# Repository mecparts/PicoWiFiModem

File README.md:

# Pico WiFi modem

## A Pico W based RS232 \<-\> WiFi modem with Hayes AT style commands and LED indicators

|  |
|:--:|
| The Pico WiFi modem |

This project began as an exercise to learn about the Pico W and lwIP.
Then, as I figured things out, it sort of took on a life of its own...

The code was ported from my 
[Retro WiFi Modem](https://github.com/mecparts/RetroWiFiModem). 
One look at it will betray its Arduino IDE origin! It's definitely not
the most efficient way to do things in the Pico world, but it worked
well enough for my purposes in learning "okay, I know what I want to do
here, but how does the Pico C/C++ SDK do it?"

It likely would have been much faster to install one of the Pico-Arduino
cores. I imagine there would have been far fewer code changes. But I
don't think I would have learned anywhere near as much about the
workings of the Pico W and lwIP as I did by using the Pico SDK.

## The Hardware

|  |
|:--:|
| The prototype |

As with the code, I re-up'd a lot of the original hardware decisions.
But, since this time around it wasn't a pandemic project that I was 
trying to do as much as possible with parts on hand, I used a MAX3237
instead of a MAX3232.

|  |
|:--:|
| The interior |

The modem still uses the classic Hayes style blinking LEDs and a DE-9F
for the RS-232 connector. Everything is displayed: RTS, CTS, DSR, DTR,
DCD, RI, TxD and RxD. And this time, since I used a MAX3237, they're all
brought out to the DE-9F connector. So things like using a change in the
DTR line to go to command mode or end a call are supported (on a system
that brings DTR out to the serial port, of course).

Since the Pico W doesn't have EEPROM on board, I added a small 4K I2C
EEPROM to the mix. I could have used a block of the Pico's flash, but I
wanted to get a feel for I2C on the Pico as well.

The Pico is socketed on this first board due to the lack of OTA
programming. The PCB is set up to allow it to be soldered directly on
the board once I have that figured out.

|  |
|:--:|
| The back panel |

The power connector expects a 2.1mm I.D. x 5.5mm O.D. barrel plug,
delivering 5 volts, centre positive.  I used a Tri-Mag L6R06H-050 (5V,
1.2A), [DigiKey part# 364-1251-ND](https://www.digikey.com/product-detail/en/tri-mag-llc/L6R06H-050/364-1251-ND/7682614).
If you plug in a 9V adapter like you'd use for an Arduino, you *will*
let the magic smoke out and have an ex-modem on your hands.

|  |
|:--:|
| The schematic |

On the off chance that there's someone else out there with a well
stocked parts box and a burning desire to put together their own Pico
WiFi modem, there's a [BOM](kicad/Pico_WiFi_Modem-bom.csv) in the
kicad sub directory. As was true with the original ESP8266 design, if
you actually had to go out and buy all the parts, it really wouldn't be
cost effective.

## The case

I re-used the same case, a Hammond 1593N case (DigiKey part #
[HM963-ND](https://www.digikey.com/en/products/detail/hammond-manufacturing/1593NBK/1090774)
or [HM964-ND](https://www.digikey.com/en/products/detail/hammond-manufacturing/1593NGY/1090775)
depending on whether you like black or grey). STL and OpenSCAD
files are included for the front and back panels. You could use the
proper Hammond red panel for the front (DigiKey part #
[HM965-ND](https://www.digikey.com/en/products/detail/hammond-manufacturing/1593NIR10/1090776)),
*but* they're only available in 10 packs and their price is highway robbery.
I ended up using a slightly smaller red panel (DigiKey part #
[HM889-ND](https://www.digikey.com/en/products/detail/hammond-manufacturing/1593SIR10/409899))
that was ~much~ cheaper (it has recently increased in price by 500%)
and available in single units.

The labels are unbelievably low tech. I print them on a piece of inkjet
transparency film. I then cut that down to size so that it will fit
under the LED opening. Then I attach the trimmed down transparency piece
to a length of matte finish, invisible tape and carefully position it in
place. A bit of careful work with an x-acto knife and you've got
yourself a label that looks like it's part of the panel. If you look
closely at the front panel image you can see the edges of the
transparency film and the tape, but in practice they both essentially
disappear.

## The PCB

The PCB includes cutouts for the two columns that join the case
together, and mounting holes for the 6 standoffs. Also, there's an oddly
shaped cutout in back end to allow a particular IDC DE-9F I had on hand.
It's available from DigiKey (or a very close clone is) but it's fairly
pricey. But there's plenty of room for an ordinary solder cup DE-9F.
You'd most likely want to omit the 10 pin header and just wire the DE-9F
right to the board.

Unlike the original Retro Wifi Modem, I made no attempt to make this
board by hand. Instead, I took advantage of an introductory offer by a
well known PCB house and had PCBs made. 5 boards for under 20 bucks, and
delivered in under a week? Who could say no?

## The Software

|  |
|:--:|
| Modem command list |

The software is naturally quite similar to the original ESP8266 Wifi
modem. There are a few changes (and one fairly major omission):

* DTR signal handling (AT&D)
* Escape sequence character definition (ATS2)
* no OTA reprogramming (yet!)

### First time setup

The default serial configuration is 9600bps, 8 data bits, no parity, 1
stop bit.

Here's the commands you need to set up the modem to automatically
connect to your WiFi network:

1. `AT$SSID=your WiFi network name` to set the WiFi network that the
modem will connect to when it powers up.
2. `AT$PASS=your WiFi network password` to set the password for the
network.
3. `ATC1` to connect to the network.
4. Optional stuff:
   * `AT$SB=speed` to set the default serial speed.
   * `AT$SU=dps` to set the data bits, parity and stop bits.
   * `ATNETn` to select whether or not to use Telnet protocol.
   * `AT&Kn` to use RTS/CTS flow control or not.
   * `AT&Dn` to set up DTR handling.
5. `AT&W` to save the settings.

Once you've done that, the modem will automatically connect to your WiFi
network on power up and will be ready to "dial up" a connection with
ATDT.

### Command Reference

Multiple AT commands can be typed in on a single line. Spaces between
commands are allowed, but not within commands (i.e. AT S0=1 X1 Q0 is
fine; ATS 0=  1 is not). Commands that take a string as an argument
(e.g. AT$SSID=, AT$TTY=) assume that *everything* that follows is a part
of the string, so no commands are allowed after them.

Command | Details
------- | -------
+++     | Online escape code. Once your modem is connected to another device, the only command it recognises is an escape code of a one second pause followed by three typed plus signs and another one second pause, which puts the modem back into local command mode.
A/      | Repeats the last command entered. Do not type AT or press Enter.
AT      | The attention prefix that precedes all command except A/ and +++.
AT?     | Displays a help cheatsheet.
ATA     | Force the modem to answer an incoming connection when the conditions for auto answer have not been satisfied.
ATC?<br>ATC*n* | Query or change the current WiFi connection status. A result of 0 means that the modem is not connected to WiFi, 1 means the modem is connected. The command ATC0 disconnects the modem from a WiFi connection. ATC1 connects the modem to the WiFi.
ATDS*n* | Calls the host specified in speed dial slot *n* (0-9).
ATDT<i>[+=-]host[:port]</i> | Tries to establish a WiFi TCP connection to the specified host name or IP address. If no port number is given, 23 (Telnet) is assumed. You can also use ATDT to dial one of the speed dial slots in one of two ways:<br><br><ul><li>The alias in each speed dial slot is checked to see if it matches the specified hostname.</li><li>A host specified as 7 identical digits dials the slot indicated by the digit. (i.e. 2222222 would speed dial the host in slot 2).</li></ul>Preceding the host name or IP address with a +, = or - character overrides the ATNET setting for the period of the connection.<br><br><ul><li>**+** forces NET2 (fake Telnet)</li><li>**=** forces NET1 (real Telnet)</li><li>**-** forces NET0 (no Telnet)</li></ul>Once the dial attempt has begun, pressing any key before the connection is established will abort the attempt.
ATE?<br>ATE*n* | Command mode echo. Enables or disables the display of your typed commands.<br><br><ul><li>E0 Command mode echo OFF. Your typing will not appear on the screen.</li><li>E1 Command mode echo ON. Your typing will appear on the screen.</li></ul>
ATGET*http&#58;//host[/page]* | Displays the contents of a website page. **https** connections are not supported. Once the contents have been displayed, the connection will automatically terminate.
ATH | Hangs up (ends) the current connection.
ATI | Displays the current network status, including sketch build date, WiFi and call connection state, SSID name, IP address, and bytes transferred.
ATNET?<br>ATNET*n* | Query or change whether telnet protocol is enabled. A result of 0 means that telnet protocol is disabled; 1 is *Real* telnet protocol and 2 is *Fake* telnet protocol. If you are connecting to a telnet server, it may expect the modem to respond to various telnet commands, such as terminal name (set with `AT$TTY`), terminal window size (set with `AT$TTS`) or terminal speed. Telnet protocol should be enabled for these sites, or you will at best see occasional garbage characters on your screen, or at worst the connection may fail.<br><br>The difference between *real* and *fake* telnet protocol is this: with *real* telnet protocol, a carriage return (CR) character being sent from the modem to the telnet server always has a NUL character added after it. The implementation of the telnet protocol used by some BBSes doesn't properly strip out the NUL character. When connecting to such BBSes (Particles! is one), use *fake* telnet.<br><br>When using *real* telnet protocol, when the telnet server sends a CR character followed by a NUL character, only the CR character will be sent to the serial port; the NUL character will be silently stripped out. With *fake* telnet protocol, the NUL will be passed through.
ATO | Return online. Use with the escape code (+++) to toggle between command and online modes.
ATQ?<br>ATQ*n* | Enable or disable the display of result codes. The default is Q0.<br><br><ul><li>Q0 Display result codes.</li><li>Q1 Suppress result codes (quiet).</li></ul>
ATRD<br>ATRT | Displays the current UTC date and time from NIST in the format *YY-MM-DD HH:MM:SS*. A WiFi connection is required and you cannot be connected to another site.
ATS0?<br>ATS0=*n* | Display or set the number of "rings" before answering an incoming connection. Setting `S0=0` means "don't answer".
ATS2?<br>ATS2=*n* | Display or set the ASCII code used in the online escape sequence. The default value is 43 (the + plus character). Setting it to any value between 128 and 255 will disable the online escape function.
ATV?<br>ATV*n* | Display result codes in words or numbers. The default is V1.<br><br><ul><li>V0 Display result codes in numeric form.</li><li>V1 Display result codes in text form.</li></ul>
ATX?<br>ATX*n* | Control the amount of information displayed in the result codes. The default is X1 (extended codes).<br><br><ul><li>X0 Display basic codes (CONNECT, NO CARRIER)</li><li>X1 Display extended codes (CONNECT speed, NO CARRIER (connect time))</li></ul>
ATZ | Resets the modem.
AT&D?<br>AT&D*n* | Display or set the handling of DTR going inactive. The default is &D0 (ignored).<br><br><ul><li>&D0 Ignore</li><li>&D1 Go to command mode</li><li>&D2 End call</li><li>&D3 Reset modem</li></ul>
AT&F | Reset the NVRAM contents and current settings to the sketch defaults. All settings, including SSID name, password and speed dial slots are affected.
AT&K?<br>AT&K*n* | Data flow control. Prevents the modem's buffers for received and transmitted from overflowing.<br><br><ul><li>&K0 Disable data flow control.</li><li>&K1 Use hardware flow control. Requires that your computer and software support Clear to Send (CTS) and Request to Send (RTS) at the RS-232 interface.</li></ul>
AT&R?<br>AT&R=*server pwd* | Query or change the password for incoming connections. If set, the user has 3 chances in 60 seconds to enter the correct password or the modem will end the connection.
AT&V*n* | Display current or stored settings.<br><br><ul><li>&V0 Display current settings.</li><li>&V1 Display stored settings.</li></ul>
AT&W | Save current settings to NVRAM.
AT&Zn?<br>AT&Z*n*=*host[:port],alias* | Store up to 10 numbers in NVRAM, where *n* is the position 0-9 in NVRAM, and *host[:port]* is the host string, and *alias* is the speed dial alias name. The host string may be up to 50 characters long, and the alias string may be up to 16 characters long.<br><br>Example: `AT&Z2=particlesbbs.dyndns.org:6400,particles`<br><br>This number can then be dialed in any of the following ways:<br><br><ul><li>`ATDS2`</li><li>`ATDTparticles`</li><li>`ATDT2222222`</li></ul>
AT$AE?<br>AT$AE=*startup AT cmd* | Query or change the command line to be executed when the modem starts up.
AT$AYT | Sends a Telnet "Are You There?" command if connected to a Telnet remote.
AT$BM?<br>AT$BM=*server busy msg* | Query or change a message to be returned to an incoming connection if the modem is busy (i.e. already has a connection established).
AT$MDNS<br>AT$MDNS=*mDNS name* | Query or change the mDNS network name (defaults to "espmodem"). When a non zero TCP port is defined, you can telnet to that port with **telnet mdnsname.local port**.
AT$PASS?<br>AT$PASS=*WiFi pwd* | Query or change the current WiFi password. The password is case sensitive. Clear the password by issuing the set command with no password. The maximum length of the password is 64 characters.
AT$SB?<br>AT$SB=*n* | Query or change the current baud rate. Valid values for "n" are 110, 300, 450, 600, 710, 1200, 2400, 4800, 9600, 19200, 38400, 57600, 76800 and 115200. Any other value will return an ERROR message. The default baud rate is 1200. The Pico WiFi modem does not automatically detect baud rate like a dial-up modem. The baud rate setting must match that of your terminal to operate properly. It will display garbage in your terminal otherwise.
AT$SP?<br>AT$SP=*n* | TCP server port to listen on. A value of 0 means that the TCP server is disabled, and no incoming connections are allowed.
AT$SSID?<br>AT$SSID=*ssid name* | Query or change the current SSID to the specified name. The given SSID name is case sensitive. Clear the SSID by issuing the set command with no SSID. The maximum length of the SSID name is 32 characters.
AT$SU?<br>AT$SU=*dps* | Query or change the current number of data bits ('d'), parity ('p') and stop bits ('s") of the serial UART. Valid values for 'd' are 5, 6, 7 or 8 bits. Valid values for 'p' are (N)one, (O)dd or (E)ven parity. Valid values for 's' are 1 or 2 bits. The default settings are 8N1. The UART setting must match your terminal to work properly.
AT$TTL?<br>AT$TTL=*telnet location* | Query or change the Telnet location value to be returned when the Telnet server issues a SEND-LOCATION request. The default value is "Computer Room".
AT$TTS?<br>AT$TTS=*WxH* | Query or change the window size (columns x rows) to be returned when the Telnet server issues a NAWS (Negotiate About Window Size) request. The default value is 80x24. For terminals that are smaller than 80x24, setting these values appropriately will enable paging on the help (AT?) and network status (ATI) commands.
AT$TTY?<br>AT$TTY=*terminal type* | Query or change the terminal type to be returned when the Telnet server issues a TERMINAL-TYPE request. The default value is "ansi".
AT$W?<br>AT$W=*n* | Startup wait.<br><br><ul><li>$W=0 Startup with no wait.</li><li>$W=1 Wait for the return key to be pressed at startup.</li></ul>

### Updating the Code

As I'm writing this, I haven't settled on an OTA programming method that
I like. But I will figure something out; taking the modem apart to do a
code update will get old the very first time I have to do it. Plus,
it means that the Pico W can't be soldered down to the PCB, and that'd
be a nice to have as well.

## Status

It's a work in progress at the moment. The lack of OTA programming is
the big "needs to be done" item.

As this is my first Pico project, and the first time I've written lwIP 
stuff (and the first time I've really had to make changes to CMake 
stuff), I've run headlong into all the usual beginner gotchas. And I'm
completely, absolutely sure that I haven't found them all yet.

The code works reasonably well at the moment; it can call out, you can 
call in, Ymodem and Zmodem transfers work, I've figured out why it used
to appear to lock up when I left it alone for 10 minutes (Wifi power
management, if you're wondering)... but I'm under no illusion that there
aren't bugs aplenty yet to be squashed. After all, I found a handful of
problems in the original ESP8266 Retro Wifi modem code while I was
getting the Pico code working, and the ESP code had been pretty much
stable for over two years.

And I think I may have also discovered why every once in a while, the
modem would get behind a few (or many) characters either on receive or
transmit. The 'volatile' qualifier isn't of as much use with variables
modified by two threads as it is with memory mapped I/O or hardware
registers. To make a long story short, '++var' and '--var' aren't
atomic operations; they're read/modify/write. And every once in a great
while the main thread would be updated a buffer length at the same time
the lwIP thread was updating the same buffer length and whackiness
ensued.

For the moment, I've taken the naive approach of surrounding the buffer
length writes with disable/re-enable interrupt calls. I think that will
work reasonably well (though if I ever decided to make use of the second
core, it'll fail because interrupts are only disabled on the calling
core). If not, it'll be time to bone up on mutexes and semaphores and
critical sections.

### Linux, Telnet, Zmodem and downloading binary files

Have you used the modem to 'dial' into a Linux box? And have you done a
`sz binary_file` on the Linux box? And at a completely reproducible
point in the file, has the connection dropped? But other binary files
work just fine? Then read on.

This drove me slightly batty for months on the original Retro modem. I
finally narrowed it down to trying to send blocks of binary data with a
large number of FF bytes. eventually created a test file consisting of
2K of FF and used that to test with. I could download it through the
modem with Xmodem just fine. Ymodem also worked if I kept the block size
down to 128 bytes - but the connection would drop instantly if I tried
sending 1K blocks. Same thing with Zmodem.

In fact, if I just tried `cat binary_file`, the connection would
drop. Which eventually got me thinking. Sitting at the console on my
main Linux box, I telnet'd to the same box and logged in. No WiFi modem
involved anywhere, just a telnet session on the console to the same box.
I then did a `cat binary_file`. The telnet connection dropped, and I
was back in my original session.

It's the Linux telnet daemon. Not the modem at all.

To prove it to myself, I hooked up WiFi modems to two systems on their
serial ports and had one dial into the other. I could send the all FF
binary file back and forth with Zmodem and Ymodem, no trouble at all.

But you really, really need to download that binary file through the
modem from a telnet connection to a Linux box? You're not going to be
able to use Zmodem. Ymodem will work (the sy command defaults to 128
byte blocks), as will Xmodem. But not Zmodem.

Oddly enough, the telnet daemon has no trouble *receiving* the all FF
binary file. Only sending it. Your guess as to why is probably better
than mine.

## References

* [Retro WiFi Modem](https://github.com/mecparts/RetroWiFiModem)
* [WiFi232 - An Internet Hayes Modem for your Retro Computer](http://biosrhythm.com/?page_id=1453)<br>
* [WiFi232's Evil Clone](https://forum.vcfed.org/index.php?threads/wifi232s-evil-clone.1070412/)<br>
* [Jussi Salin's Virtual modem for ESP8266](https://github.com/jsalin/esp8266_modem)<br>
* [Stardot's ESP8266 based virtual modem](https://github.com/stardot/esp8266_modem)<br>
* [Roland Juno's ESP8266 based virtual modem](https://github.com/RolandJuno/esp8266_modem)

## Acknowledgements

* A whole lot of people owe a big vote of thanks to Jussi Salin for
releasing their virtual modem code for the ESP8266 and starting the
ball rolling.
* Paul Rickards for an amazing bit of hardware to draw inspiration from.
* All the Stardot contributors for their work.
* And, of course, Dennis C. Hayes for creating something so simple and
elegant that has stood the test of time.

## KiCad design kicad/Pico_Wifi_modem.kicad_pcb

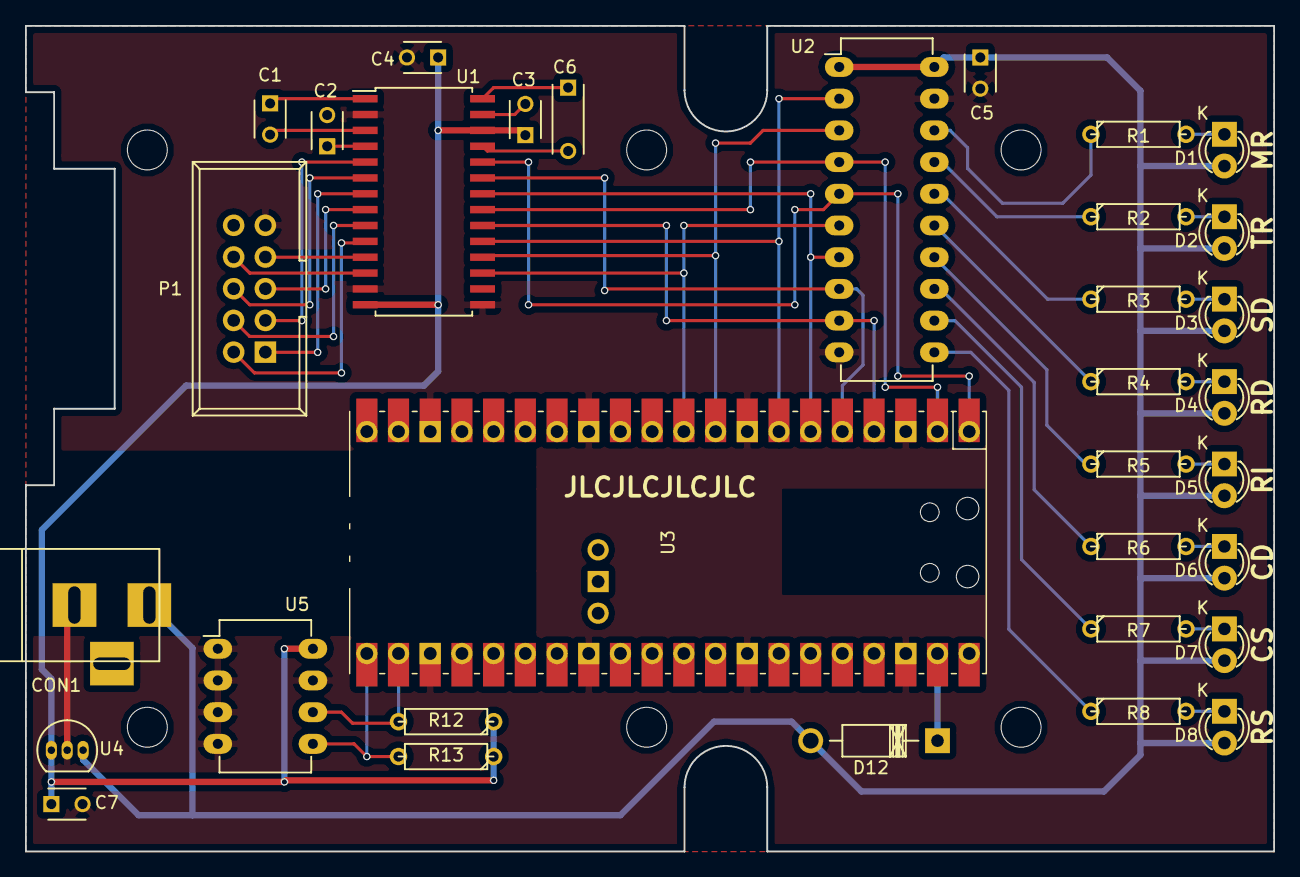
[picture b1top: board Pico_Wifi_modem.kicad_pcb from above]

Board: 2 copper layers, 100.0 x 66.1 mm, 33 parts (0 on the bottom side), 44 nets.

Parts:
C1, C2, C3, C4, C5: 100nF; C_Disc_D3_P2.5
C6: 100nF; C_Disc_D3_P5
C7: 1uF; C_Disc_D3_P2.5
CON1: BARREL_JACK
D1, D2, D3, D4, D5, D6, D7, D8: TLPR5600; LED-3MM
D12: 1N5817; Diode_DO-41_SOD81_Horizontal_RM10
P1: CONN_02X05; IDC_Header_Straight_10pins
R1, R2, R3, R4, R5, R6, R7, R8: 560R; R3
R12, R13: 3.9K; R3
U1: MAX3237CAI+; SOIC-28W_7.5x17.9mm_Pitch1.27mm
U2: 74HCT245; DIP-20_W7.62mm_LongPads
U3: Pico; RPi_PicoW
U4: LM2950ACZ-3.3; TO-92_Inline_Narrow_Oval
U5: 24LC32; DIP-8_W7.62mm_LongPads

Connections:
+3V3: C3.1, C4.1, C7.1, R12.1, R13.1, U1.14, U1.26, U4.1, U5.8
+5V: C5.1, CON1.1, D1.2, D2.2, D3.2, D4.2, D5.2, D6.2, D7.2, D8.2, D12.2, U2.1, U2.20, U4.3
GND: C2.2, C4.2, C5.2, C7.2, CON1.2, P1.9, U1.2, U1.13, U1.15, U2.10, U2.19, U3.3, U3.8, U3.13, U3.18, U3.23, U3.28, U3.33, U3.38, U4.2, U5.1, U5.2, U5.3, U5.4, U5.7
unnamed: C1.1, U1.1
unnamed: C1.2, U1.3
unnamed: C2.1, U1.4
unnamed: C3.2, U1.27
unnamed: C6.1, U1.28
unnamed: C6.2, U1.25
unnamed: D1.1, R1.2
unnamed: D2.1, R2.2
unnamed: D3.1, R3.2
unnamed: D4.1, R4.2
unnamed: D5.1, R5.2
unnamed: D6.1, R6.2
unnamed: D7.1, R7.2
unnamed: D8.1, R8.2
unnamed: D12.1, U3.39
unnamed: P1.1, U1.7
unnamed: P1.2, U1.10
unnamed: P1.3, U1.5
unnamed: P1.4, U1.9
unnamed: P1.5, U1.8
unnamed: P1.6, U1.6
unnamed: P1.7, U1.11
unnamed: P1.8, U1.12
unnamed: R1.1, U2.18
unnamed: R2.1, U2.17
unnamed: R3.1, U2.16
unnamed: R4.1, U2.15
unnamed: R5.1, U2.14
unnamed: R6.1, U2.13
unnamed: R7.1, U2.12
unnamed: R8.1, U2.11
unnamed: R12.2, U3.22, U5.6
unnamed: R13.2, U3.21, U5.5
unnamed: U1.17, U2.6, U3.10
unnamed: U1.18, U2.3, U3.9
unnamed: U1.19, U2.2, U3.7
unnamed: U1.20, U2.9, U3.4
unnamed: U1.21, U2.4, U3.2
unnamed: U1.22, U2.7, U3.6
unnamed: U1.23, U2.8, U3.5
unnamed: U1.24, U2.5, U3.1

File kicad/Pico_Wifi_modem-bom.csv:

Reference,Quantity, Value, Price, DigiKey PN
P1,1,CONN_02X05,0.41,ED1543-ND
D1-D8,8,TLPR5600,6.4,TLPR5600-ND
C1-C5,5,100nF,1.55,399-9859-1-ND
C6,1,100nF,0.33,399-9843-ND
C7,1,1uF,2.54,399-3529-ND
CON1,1,BARREL_JACK,1.09,839-54-00166-ND
R1-R8,8,560R,1.28,CF18JT560RCT-ND
U3,1,Pico W,8.88,2648-SC0918CT-ND
U4,1,LM2950ACZ-3.3,1.26,LP2950ACZ-3.3GOS-ND
U1,1,MAX3237ECDWR,5.37,296-36945-1-ND
D12,1,1N5817,0.47,N5817-TPCT-ND
U5,1,AT24C32E-PUM,0.98,AT24C32E-PUM-ND
R12-R13,2,3.9K,0.32,CF18JT3K90CT-ND
U2,1,74HCT245,1.42,296-1612-5-ND
,1,Hammond 1593NBK case,9.26,HM963-ND 
,1,Hammond red panel,0.88,HM889-ND 
,50,PCB screws,12.46,HM1442-ND
,1,5V wall adapter,8.92,364-1251-ND 
,1,DE-9F IDC connector,19.9,5746861-4-ND
,2,D-sub jackscrew,0.94,2057-JS-02-ND
,1,8 pin DIP socket,0.44,1175-1475-ND
,1,20 pin DIP socket,0.67,1175-1479-ND
,1,10 pos IDC socket,0.69,1175-1443-ND 
,1,10 cond ribbon cable,0.95,3M157815-1-ND

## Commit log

2022-09-30 Change tcpReadByte to return all text in rxBuff[] at end of call.
2022-10-01 tcpReadByte now returns -1 rxBuff empty rather than waiting I've kept the optional timeout for a few special cases but now the default operation matches what the ESP8266 WifiClient readbyte call woul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
2022-10-02 Added Hayes-style S2 (escape sequence character) support. Allow changing (or even disabling) the character used to go from online to online command mode. Disabling it saves problems when both ends of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
2022-10-02 TCP pacing and ending endless loop of Telnet commands 1. I have code that gets the remote end to (eventually) pausing sending packets. I'd tried something similar early on but didn't realize that it 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
2022-10-08 Separated out some debugging stuff, added program size to ATI
2022-10-09 Modified directory structure. Made DTR handling work immediately.
2022-10-09 Added front & back panel files
2022-10-09 Added schematic and PCB files
2022-10-09 Added license file and initial readme.
2022-10-10 Added updated bill of materials
2022-10-10 Added free heap, program size and free flash info display
2022-10-11 DTR handling, more volatiles, tighten up online escape timing 1. Once I got a serial bracket for one of my Linux boxes and set the modem up as a dialin port, I discovered that I needed to reset the '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
2022-10-12 Tracked down how head and tail ended up out of sync in txBuff If tcpSend got called by the lwIP thread when it's been called by the main thread (from tcpWriteBuf), the queue was catfu'd. Moving cyw43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
2022-10-12 Turn off Wifi power saving mode fix to prevent Wifi "going away". 5-10 minutes of no data being sent to Wifi resulted in an apparently hung system. The Pico W didn't even respond to pings. Though as 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
2022-10-13 Updated the readme file
2022-10-13 Retransmit data later if tcp_write fails Only update txBuff head and len if tcp_write succeeds, allowing data to be re-tried later on, either from tcpSent or tcpPoll.
2022-10-13 Add schematic image
2022-10-14 Removed a bit of debugging code
2022-10-14 README.md tweaks
2022-10-14 Added images
2022-10-15 First stab at a solution for buffer ptrs getting out of sync Long story short: adding 'volatile' does little for variables being written to by two threads, like the buffer lengths. I couldn't figure 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
2022-10-16 Added image of the builtin help to the readme file
2022-10-16 Pointed the readme to the correct command list image
2022-10-16 Had the SD & RD LEDs reversed: fixed It'd be easy enough to criss cross R3 and R4 and use the original PCB, but it was easy enough to fix as well.
2022-10-17 Fixed a minor bug in ATH that's been there since the beginning
2023-06-10 Added a "how to use it" bit in the readme for the label PDF file and noted the recent price hike on the red LED panel.
2023-06-13 Getting around to commit'ing some HW flow tweaks and other minutae
2023-12-30 Fixed a spelling mistake at added in the missing ATS2 doc.
